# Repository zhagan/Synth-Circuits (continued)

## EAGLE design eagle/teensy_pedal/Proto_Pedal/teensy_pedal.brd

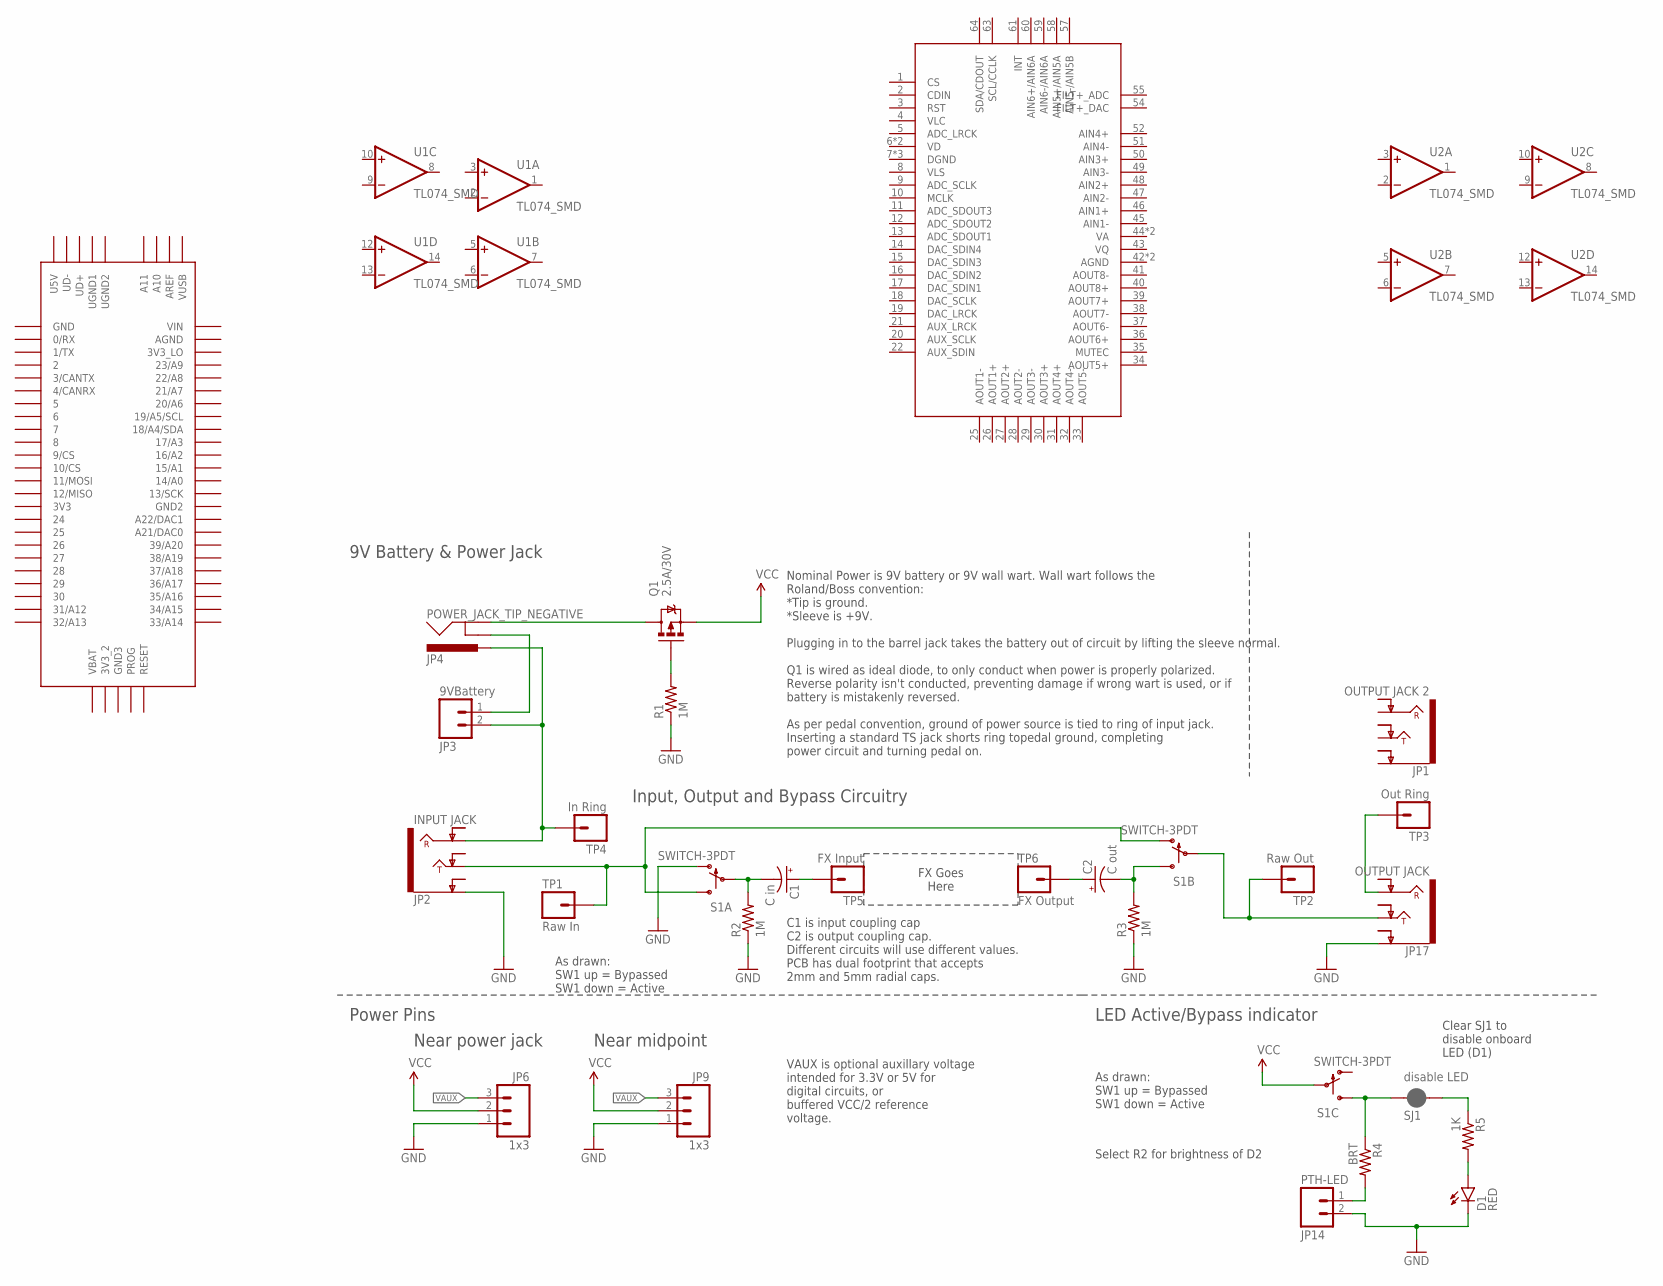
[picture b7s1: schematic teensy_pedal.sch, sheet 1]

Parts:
C1: C in; DUAL-CAP
C2: C out; DUAL-CAP
D1: RED; LED-0603
JP1: OUTPUT JACK 2; AUDIO-JACK-.25-INCH-HORIZ-PTH
JP2: INPUT JACK; AUDIO-JACK-.25-INCH-HORIZ-PTH
JP3: 9VBattery; 1X02_LONGPADS
JP4: POWER_JACK_TIP_NEGATIVE; POWER-BARRELJACK-PTH-LOCK-FIXED
JP6, JP9: 1x3; 1X03_NO_SILK
JP14: PTH-LED; 1X02_LONGPADS
JP17: OUTPUT JACK; AUDIO-JACK-.25-INCH-HORIZ-PTH
Q1: 2.5A/30V; SOT23-3
R1, R2, R3: 1M; 0603-RES
R4: BRT; AXIAL-0.3
R5: 1K; 0603-RES
S1: SWITCH-3PDT; STOMP-SWITCH-3PDT
SJ1: disable LED; PAD-JUMPER-2-NC_BY_PASTE_YES_SILK_FULL_BOX
TP1: Raw In; 1X01_NO_SILK
TP2: Raw Out; 1X01_NO_SILK
TP3: Out Ring; 1X01_NO_SILK
TP4: In Ring; 1X01_NO_SILK
TP5: FX Input; 1X01_NO_SILK
TP6: FX Output; 1X01_NO_SILK
U1, U2: TL074_SMD; SO14
U$1: CS42448; LQFP64
U$2: TEENSY_3.5/3.6

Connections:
AGND: U$1.42 (AGND), U$1.56 (AGND)
DGND: U$1.7 (DGND), U$1.23 (DGND), U$1.62 (DGND)
FILT+_ADC: U$1.55 (FILT+_ADC)
FILT+_DAC: U$1.54 (FILT+_DAC)
FX_IN: C1.P$2 (-), C1.P$3 (-), R2.2, S1.P$2
FX_OUT: C2.P$2 (-), C2.P$3 (-), R3.2, S1.P$6 (S)
GND: D1.C, JP2.SLEEVE (EARTH), JP6.1, JP9.1, JP14.2, JP17.SLEEVE (EARTH), R1.1, R2.1, R3.1, S1.P$1 (O)
LEDA: JP14.1, R4.P$2 (2)
unnamed: D1.A, R5.2
unnamed: R4.P$1 (1), S1.P$9 (S), SJ1.1
unnamed: JP3.1, JP4.SLEEVE-NORMAL (SLEEVEBREAK)
unnamed: JP2.RING, JP3.2, JP4.TIP, TP4.1
unnamed: R5.1, SJ1.2
unnamed: JP17.RING, TP3.1
unnamed: C1.P$1 (+), TP5.1
unnamed: C2.P$1 (+), TP6.1
unnamed: JP2.TIP, S1.P$3 (S), S1.P$4 (O), TP1.1
unnamed: JP17.TIP, S1.P$5, TP2.1
unnamed: Q1.1 (G), R1.2
V+: U1.4 (V+), U2.4 (V+)
V-: U1.11 (V-), U2.11 (V-)
VA: U$1.44 (VA), U$1.53 (VA)
VAUX: JP6.3, JP9.3
VBATT: JP4.SLEEVE, Q1.3 (D)
VCC: JP6.2, JP9.2, Q1.2 (S), S1.P$8
VD: U$1.6 (VD), U$1.24 (VD)
VLC: U$1.4 (VLC)
VLS: U$1.8 (VLS)
VQ: U$1.43 (VQ)

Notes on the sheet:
Power Pins
Near midpoint
Clear SJ1 to disable onboard LED (D1)
As drawn: SW1 up = Bypassed SW1 down = Active
FX Goes Here
9V Battery & Power Jack
Input, Output and Bypass Circuitry
Near power jack
LED Active/Bypass indicator
Nominal Power is 9V battery or 9V wall wart. Wall wart follows the Roland/Boss convention: *Tip is ground. *Sleeve is +9V. Plugging in to the barrel jack takes the battery out of circuit by lifting the sleeve normal. Q1 is wired as ideal diode, to only conduct when power is properly polarized. Reve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
VAUX is optional auxillary voltage intended for 3.3V or 5V for digital circuits, or buffered VCC/2 reference voltage.
C1 is input coupling cap C2 is output coupling cap. Different circuits will use different values. PCB has dual footprint that accepts 2mm and 5mm radial caps.
Select R2 for brightness of D2

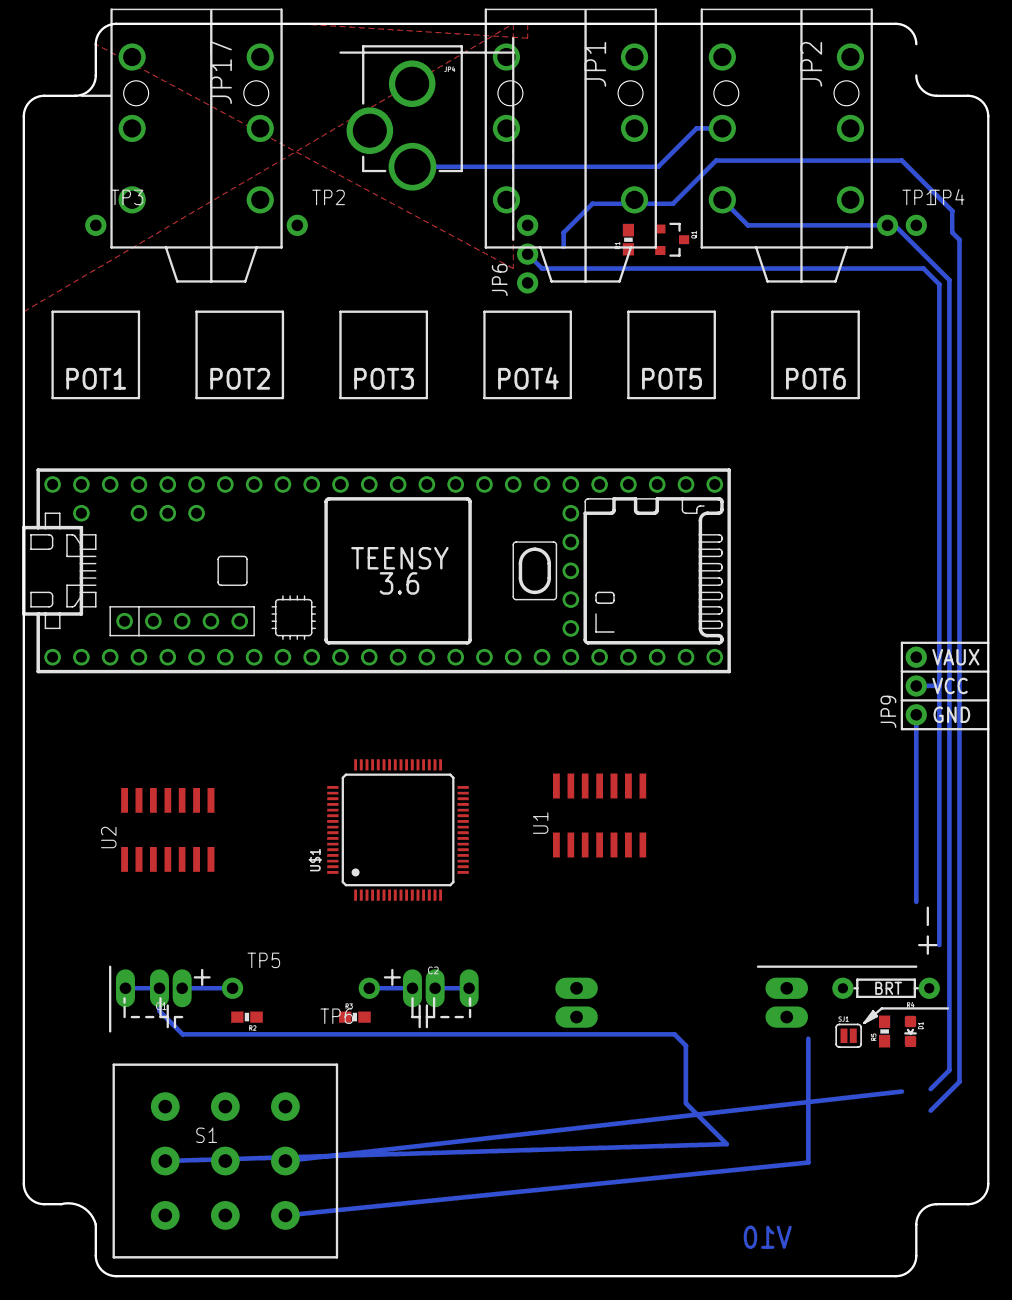
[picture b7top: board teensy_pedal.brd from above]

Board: 2 copper layers, 85.1 x 110.5 mm, 29 parts (0 on the bottom side), 24 nets.

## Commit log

2017-11-02 inital commit
2018-03-25 add euro buffer
2018-03-28 name change
2018-03-28 git ignore
2018-03-28 git cleanup
2018-03-29 dual xr readme update
2018-03-29 buff mult readme
2018-03-29 readme
2018-03-29 organization is key
2018-03-30 removed 2cd readme
2018-03-30 a clean house
2018-05-18 xr-vco-panel.zip added
2018-05-18 buff mult panel.zip added
